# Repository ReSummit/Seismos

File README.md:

# Seismos

An evolution of the Zebra keyboard, but can be used for everyday typing. Switch between ortholinear for macro keypads and staggered for typing on the go.

Since this design utilizes daughter boards, you can even choose to move the columns around with a different rail system from the example one provided.

Allows for an interchangeable configuration between 4 and 5 row keys per column. With both halves of the keyboard, you can have a maximum of 68 keys (+2 encoder switches).

**NOTE:** If you had downloaded gerber files before December 5th, 2023, ***redownload*** the files as the RGB lights were not wired correctly. Apparently KiCAD displays the back side from the top perspective... doh! This is fixed. I also fixed the power switch so that sliding it up turns on the keyboard rather than this not being congruent on both sides.

## Pictures / Example Column Shifts:
<div style="display: flex; justify-content: center;">
    <figure>
        
    </figure>
    <figure>
        
    </figure>
    <figure>
        
    </figure>
</div>

# PCB Library Structure

NOTE: If you check the PCB for DRC errors, most of them will come from either the keyboard_reversible.pretty footprint or the switch footprints inherited from the MiRage keyboard. Since both have been used before, they can be ignored.

## Libraries
All PCBs in the `pcbs` folder refer to the footprint and symbol libraries found in `libs/Seismos-libs` as well as `libs/keyboard_reversible.pretty`.

Wait, keyboard_reversible.pretty isn't in the git clone? You need to run git submodule initialization and update with this command:
```bash
git submodule update --init --recursive
```

After this, you should not get errors on missing libraries.

## Current State of PCBs
Since release v2.0.0, there are now PCBs that incorporate the 74HC595A shift register. Thanks to drFaustroll (from QMK Discord) on an example schematic for the shift register. With this shift register, displays are now on their own I2C / SPI bus and two pins are dedicated to split communications. 2 pins are now free so I have openned up these pins at the bottom of the keyboard on the front side. These ARE NOT compatible with the I2C variants of the keyboards unless you are not using the displays and will need some modification of the firmware, so choose carefully!

***WARNING***: If you are planning to use a display on this keyboard, note that nice!view compatibility with the I2C PCBs only applies for wireless builds only! Annoyingly, the nice!view does not use an ***I2C*** interface; it uses an ***SPI*** interface to work (***whyyyyyyy***). I considered moving the CS pin to the headphone jack, but this means that one of the hardware pins for I2C is not connected so this did not happen. Normal 4 pin I2C SSD1306 displays will work for wired or wireless builds however assuming that all communications happen on I2C.

There are column and thumb cluster layouts for 4 and 5 keys (however, thumb cluster can only have 4 max). This means you can get a max total of 68 keys, plus two if you are using the rotary encoders as buttons.

For this release, there are PCBs for 4 and 5 columns. Currently, the left, right, and columns are made with a maximum size of 7x5 keys per side. Something to know is that due to routing efficiency, the column order is reversed for the right side; however, row number remains the same from top to bottom.

With release v1.1.2, the PCBs are now fully tested and ready to be used. Still, read through the notes for building this keyboard a couple sections below so you know what you're getting into.

## PCB Design Thoughts
Theoretically, since JST SH connectors are pretty small, we can possibly a maximum of 12 pins, which means that you can get at most ~7 rows per column... if the microcontroller has that many pins!

Some future design thoughts:
* A suggestion to reduce pin count is to wire the 1x4 keys as a 2x2 key setup to save pins; however, this results in a 2x2n keyboard layout, which will likely be a pain... Still interesting though to point out.
* ZMK has a pull request that introduced charlieplexing, which will reduce the pin count. If this is done per half, it may be possible to have a 70% keyboard on both sides with 10 rows per column (5 forward diodes, 5 backwards diodes). There's quite a lot of room here but currently it is still in development.

# Important notes for building keyboard

For the JST SH cables, note that the male to male connector tips should face the same side. An example one is shown below (note it is a 9 pin JST SH cale, but should be the same for 10 pin JST cables).

Example of JST SH cable with male-to-male connectors facing the same side.
<div style="display: flex; justify-content: center;">
    <figure>
        
    </figure>
</div>

Soldering the JST SH connectors is not easy! It is recommended to use the stencil design that is provided along with the stencil jig, hot plate, and solder paste. Otherwise, use a soldering iron and rely on flux!

After you are done building the core and mantle PCBs, there are example firmware files provided. Please checkout the `firmware_example` folder for more details. (Unfortunately, I haven't gotten to QMK yet, so that will have to wait for a bit)

# Required PCBs to upload

For PCBs, you will need the following:
* Minimum 2 core PCBs for left and right hands
* At least 14 mantle PCBs, 7 per core PCB
    * To save on cost, you may want to just stick with 20 of one type of mantle. 5 or 4 rows are usually enough

### **NOTE:** For the Core PCBs, you wil need to choose if you want I2C only or with a shift register starting from release v2.0.0. If you want to minimize components needed **and you are sure that you have an ATMEGA microcontroller**, you should choose I2C only. If you are not sure, you should choose I2C with shift register and just get the 74HC595A.

# BOM
## Required
* (**If using shift register version**) 2x 74HC595A SOIC-16 shift registers, though you may want extras just in case
* 28 x 10 position JST SH individual wires and connectors (preferrably 10cm long). Aliexpress has these with different colors like cable mods.
    * NOTE: For these links, they come from the same seller. Contact the seller after placing a temporary order to reduce shipping costs before paying!
    * Wires: https://www.aliexpress.us/item/3256802676433370.html (choose colors, **10 cm**, and **double head**)
        * For 5 rows, 10 cm is typically enough; you may be surprised at how far the columns can go with this. However, if you plan on changing the case design, you may need 15 cm if your columns need to go farther.
    * Connectors: https://www.aliexpress.us/item/3256802084257935.html (choose **10 pin** and **SMD Horizontal**)
* Parts that can be found from Typeractive.xyz:
    * 2 x EVQPUC02K reset button
    * 2 x SSSS811101 (alternatively on Aliexpress, MSK-12C01 or SW-12C01N-GY18)
    * 2 x 110 mAH battery (since TRRS does not have 5V, you need batteries; may change later)
* 2 x nice!nano (or Arduino Pro Micro compatible footprint)
* 56-70 x 1N4148W Diodes (variable number depending on how many keys you want)
* M3 assorted length screws (see case section for more details)
* 56-70 x MX / Choc PCB Sockets (1511 for MX or 1350 for Chocs)

## Optional
* 56-68 x SK6812MINI-E for RGB
    * 6 x per column from center of keyboard + 4 for each thumb cluster
        * Example: left and right sides require 80 total for all columns. If you only need 5 columns, then you need 68.
* 2 x nice!view (or OLED, but won't be aligned to center of microcontroller)
* 4 x 12 pin low profile socket pin headers for socketed microcontrollers (or similar)
* 2 x Rotary encoder EC11 (similar to Sofle)
* 2 x PJ320A headphone jacks 
    * **NOTE**: Due to me wanting to allow for wireless or wired setups, **the current PCB design will not charge the other keyboard side**. This is because VCC is disconnected to avoid blowing up the charging circuit of the nice!nano. If you need it, bridge the connector near one of the headphone jack pins.
* 2 x 4.7k SMD resistors for I2C. This is only needed if you plan on using I2C for split communications. There's not enough space for THT versions so uh sorry :(.

# Case
Curious to see what it looks like? Behold, OnShape link that contains questionable features that are unlabelled... This case works with the PCBs and allows for sliding rails, but won't lock the rails. A better design is in the works, but this is a good start.

Currently, a better design is in the works to place the rails underneath the PCB instead of above; this would allow the keyboard to be more low profile. For now, this works.

**This design requires the following additional parts:**
* Countersunk M3 screws:
    * 24 M3x12mm
        * Mounts down the PCB to each column plate frame into the bottom stopper
    * 3 M3x8mm
        * Holds down the rails for the keyboard
    * 14 M3x6mm
        * Corresponding nuts for the top stopper screws located near the top of each column needed
    * 2 M3x5mm
        * For the holes near the encoder and display

<p align="center">
    <p>Onshape Document (click on picture):</p>
    
</p>

# More Pictures
<div style="display: flex; justify-content: center;">
    More pictures of build:
    <figure>
        
    </figure>
    <figure>
        
    </figure>
    Development case design:
    <figure>
        
    </figure>
    <figure>
        
    </figure>
</div>

# References

Seismos uses elements found from multiple places for footprints, symbols, and even the idea.

The idea for this keyboard was inspired from the [Zebra keyboard](https://github.com/nezumee/zebra). It uses jumper cables but looks to be mainly for having a physical means to determine the layout.

For footprints, they are derived from multiple places:
* [SnapEDA](https://snapeda.com) for initial 9 position JST SH footprints and models.
* [EasyEDA](https://easyeda.com) for the power switch, reset button, and 10 position JST SH footprints as well as some models.
* [Corne](https://github.com/foostan/crkbd) repository for the SK6812MINI-E footprint.
    * Fork from [petejohanson](https://github.com/petejohanson/crkbd/tree/board/corne-ultralight) for guide on nice!view pin connections.
* [Sofle](https://github.com/josefadamcik/SofleKeyboard) keyboard for rotary encoder and headphone jack footprints.
    * [Hayden Hu's PJ320A model](https://grabcad.com/library/pj320a-pj320d-3-5mm-jack-10) was used to show the headphone jack on the 3D viewer.
    * [Dmitry Levin's EC11 encoder models](https://grabcad.com/library/11mm-metal-shaft-rotary-encoders-tht-vertical-w-push-on-switch-1) was used to show the encoder on the 3D viewer.
* [keyboard_reversible.pretty](https://github.com/50an6xy06r6n/keyboard_reversible.pretty) for easy reverse footprints made for the Pro Micro.
* [Zack Freedman's MiRage Keyboard](https://github.com/ZackFreedman/MiRage) for Choc / MX footprints with modifications to include SK6812MINI-E within the footprint.
    * [Dennis Lee's Kailh 1350 socket model](https://grabcad.com/library/kailh-1350-socket-20) was used to show the switch socket on the 3D viewer.

In the libs folder, there may be other files regarding other footprints such as the EVQPUC02K. This was found on EasyEDA on early attempts to extract the footprints.
There is also the MSK-12C02 switch. This was found from [mzst's blog](https://mzstblog.blogspot.com/2016/01/msk-12c02-smd-slider-switch-spdt-eagle.html) website, which was a good reference for the switch, but I ended up using the symbol and combined with the other footprint found from EasyEDA. Archived here as well bvecause it is nice to have a backup of it.

For firmware, there are QMK, ZMK, and KMK. Only QMK has support for shift registers at the moment but I will get to the other firmwares at some point. QMK's firmware is somewhat based from the Sofle code already on the qmk_firmware, especially the oled implementation, which is untested. Also, the LICENSE may need to be updated; will check this later.

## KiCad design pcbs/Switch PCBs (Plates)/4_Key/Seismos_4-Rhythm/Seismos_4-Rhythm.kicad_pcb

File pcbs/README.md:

# Required PCBs to upload

Thank you for downloading the PCB files! For PCBs, you will need the following:
* Minimum 2 core PCBs for left and right hands
* At least 14 mantle PCBs, 7 per core PCB
    * For cost, you may want to just stick with 20 of one type of mantle. 5 or 4 rows are usually enough

### **NOTE:** For the Core PCBs, you wil need to choose if you want I2C only or with a shift register. If you want to minimize components needed **and you are sure that you have an ATMEGA microcontroller**, you should choose I2C only. If you are not sure, you should choose I2C with shift register and just get the 74HC595A.

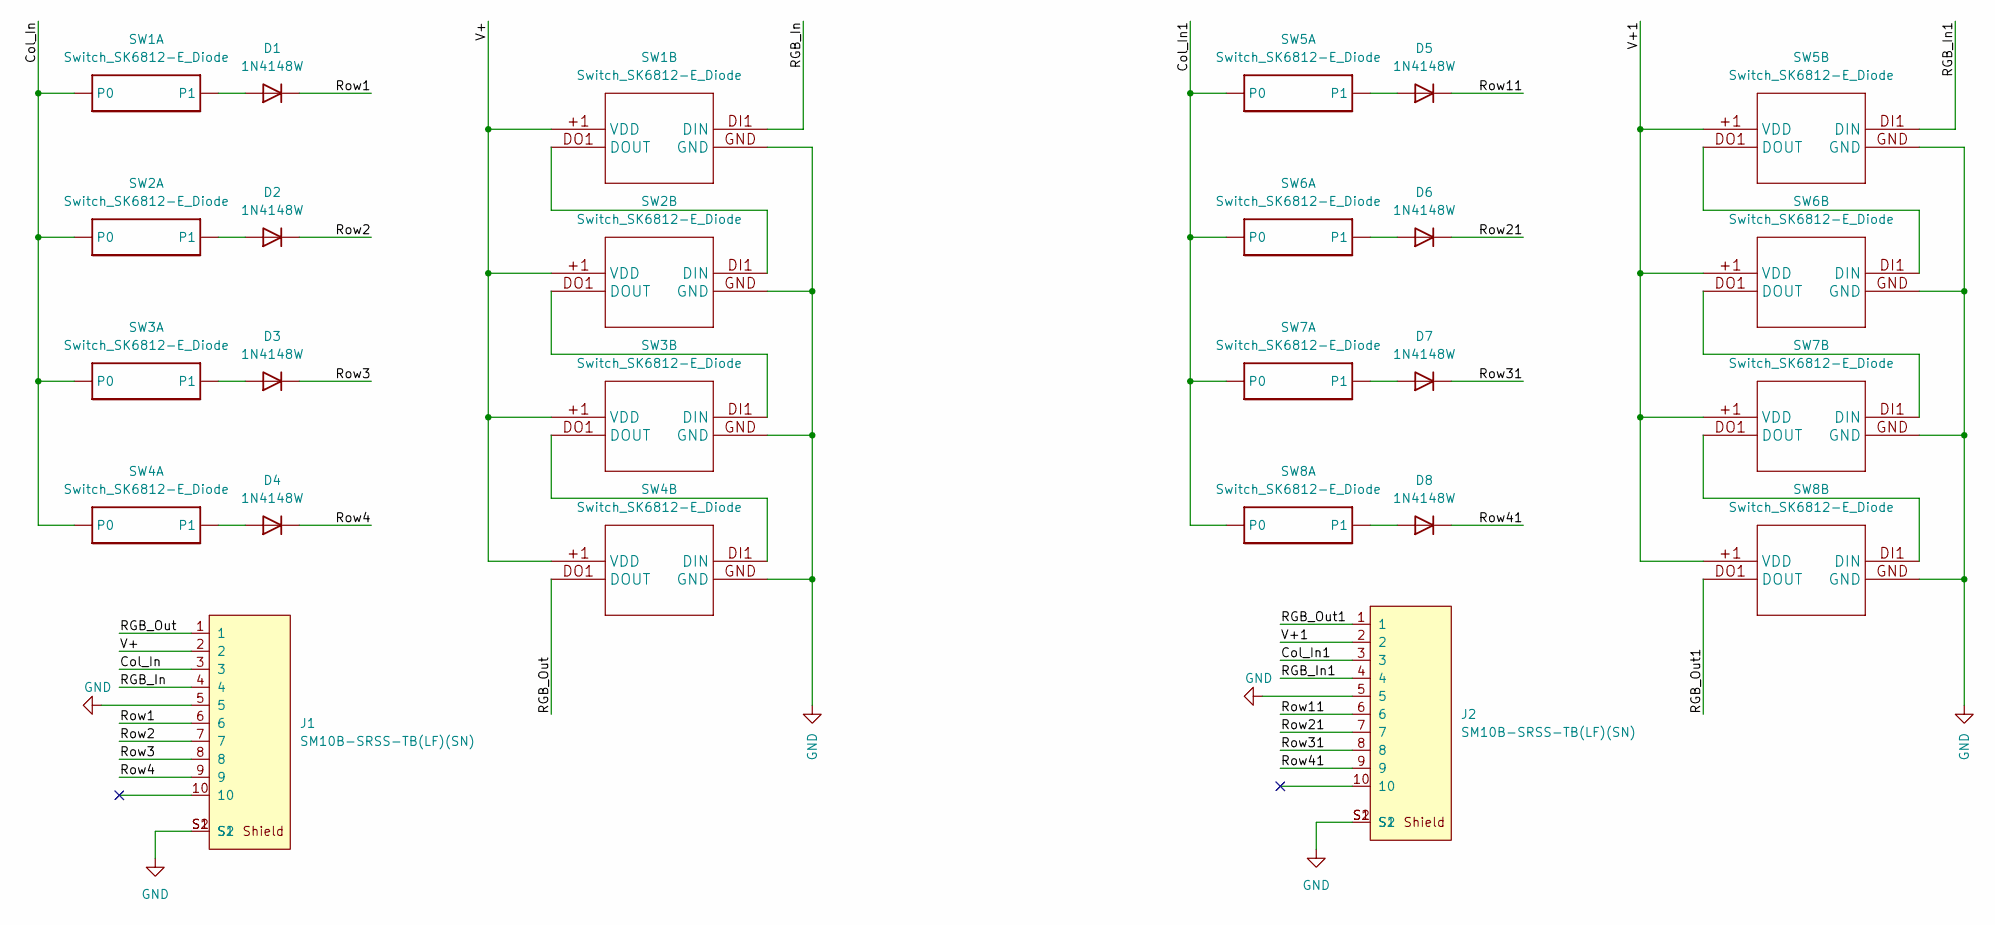
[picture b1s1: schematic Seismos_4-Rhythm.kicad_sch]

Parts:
D1, D2, D3, D4, D5, D6, D7, D8: 1N4148W; D_SOD-123
J1, J2: SM10B-SRSS-TB(LF)(SN); CONN-SMD_10P-P1.00_SM10B-SRSS-TB-LF-SN; PARTREV 1.0
SW1, SW2, SW3, SW4, SW5, SW6, SW7, SW8: Switch_SK6812-E_Diode

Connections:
/Col_In: J1.3, SW1.CHOC2 (P0), SW1.MX2 (P0), SW2.CHOC2 (P0), SW2.MX2 (P0), SW3.CHOC2 (P0), SW3.MX2 (P0), SW4.CHOC2 (P0), SW4.MX2 (P0)
/Col_In1: J2.3, SW5.CHOC2 (P0), SW5.MX2 (P0), SW6.CHOC2 (P0), SW6.MX2 (P0), SW7.CHOC2 (P0), SW7.MX2 (P0), SW8.CHOC2 (P0), SW8.MX2 (P0)
/RGB_In: J1.4, SW1.DI1 (DIN)
/RGB_In1: J2.4, SW5.DI1 (DIN)
/RGB_Out: J1.1, SW4.DO1 (DOUT)
/RGB_Out1: J2.1, SW8.DO1 (DOUT)
/Row1: D1.1 (K), J1.6
/Row2: D2.1 (K), J1.7
/Row3: D3.1 (K), J1.8
/Row4: D4.1 (K), J1.9
/Row11: D5.1 (K), J2.6
/Row21: D6.1 (K), J2.7
/Row31: D7.1 (K), J2.8
/Row41: D8.1 (K), J2.9
/V+: J1.2, SW1.+1 (VDD), SW2.+1 (VDD), SW3.+1 (VDD), SW4.+1 (VDD)
/V+1: J2.2, SW5.+1 (VDD), SW6.+1 (VDD), SW7.+1 (VDD), SW8.+1 (VDD)
GND: J1.5, J1.S1, J1.S2, J2.5, J2.S1, J2.S2, SW1.GND, SW2.GND, SW3.GND, SW4.GND, SW5.GND, SW6.GND, SW7.GND, SW8.GND
unnamed: D1.2 (A), SW1.CHOC1 (P1), SW1.MX1 (P1)
unnamed: D2.2 (A), SW2.CHOC1 (P1), SW2.MX1 (P1)
unnamed: D3.2 (A), SW3.CHOC1 (P1), SW3.MX1 (P1)
unnamed: D4.2 (A), SW4.CHOC1 (P1), SW4.MX1 (P1)
unnamed: D5.2 (A), SW5.CHOC1 (P1), SW5.MX1 (P1)
unnamed: D6.2 (A), SW6.CHOC1 (P1), SW6.MX1 (P1)
unnamed: D7.2 (A), SW7.CHOC1 (P1), SW7.MX1 (P1)
unnamed: D8.2 (A), SW8.CHOC1 (P1), SW8.MX1 (P1)
unnamed: SW1.DO1 (DOUT), SW2.DI1 (DIN)
unnamed: SW2.DO1 (DOUT), SW3.DI1 (DIN)
unnamed: SW3.DO1 (DOUT), SW4.DI1 (DIN)
unnamed: SW5.DO1 (DOUT), SW6.DI1 (DIN)
unnamed: SW6.DO1 (DOUT), SW7.DI1 (DIN)
unnamed: SW7.DO1 (DOUT), SW8.DI1 (DIN)

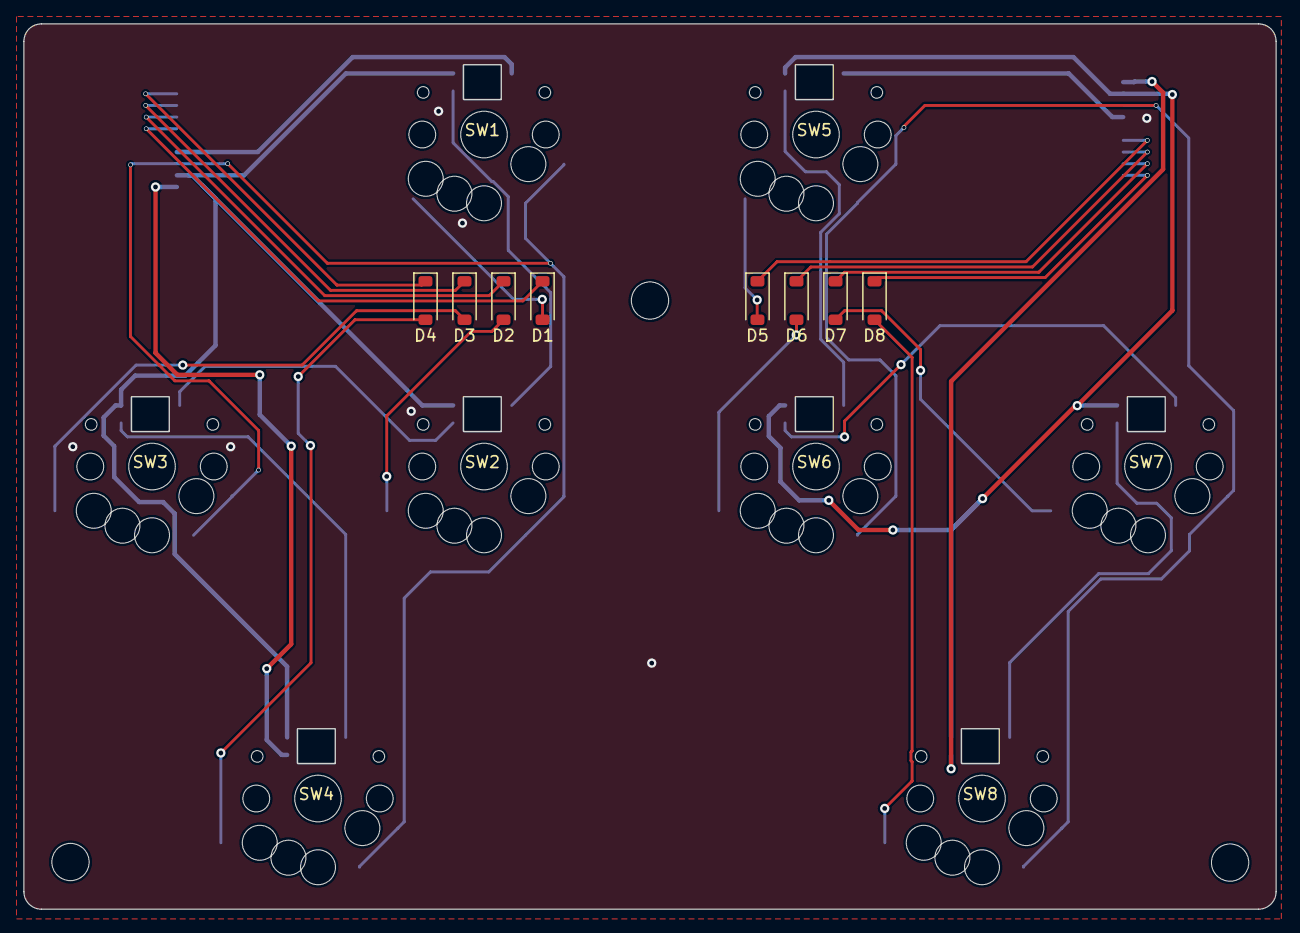
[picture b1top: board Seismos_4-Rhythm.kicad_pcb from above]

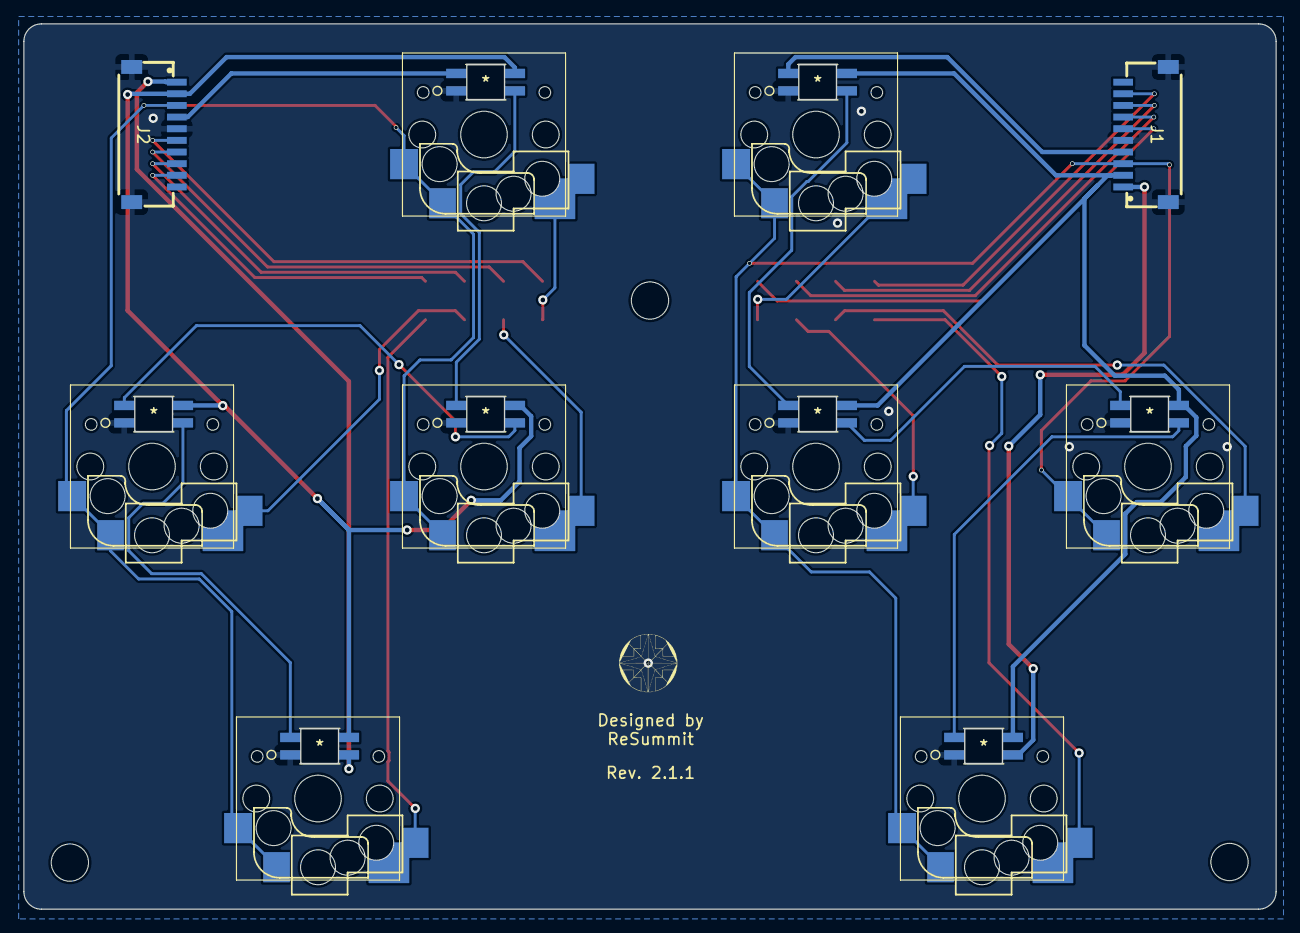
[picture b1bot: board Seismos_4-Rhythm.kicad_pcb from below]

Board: 2 copper layers, 107.5 x 76.0 mm, 18 parts (10 on the bottom side), 31 nets.

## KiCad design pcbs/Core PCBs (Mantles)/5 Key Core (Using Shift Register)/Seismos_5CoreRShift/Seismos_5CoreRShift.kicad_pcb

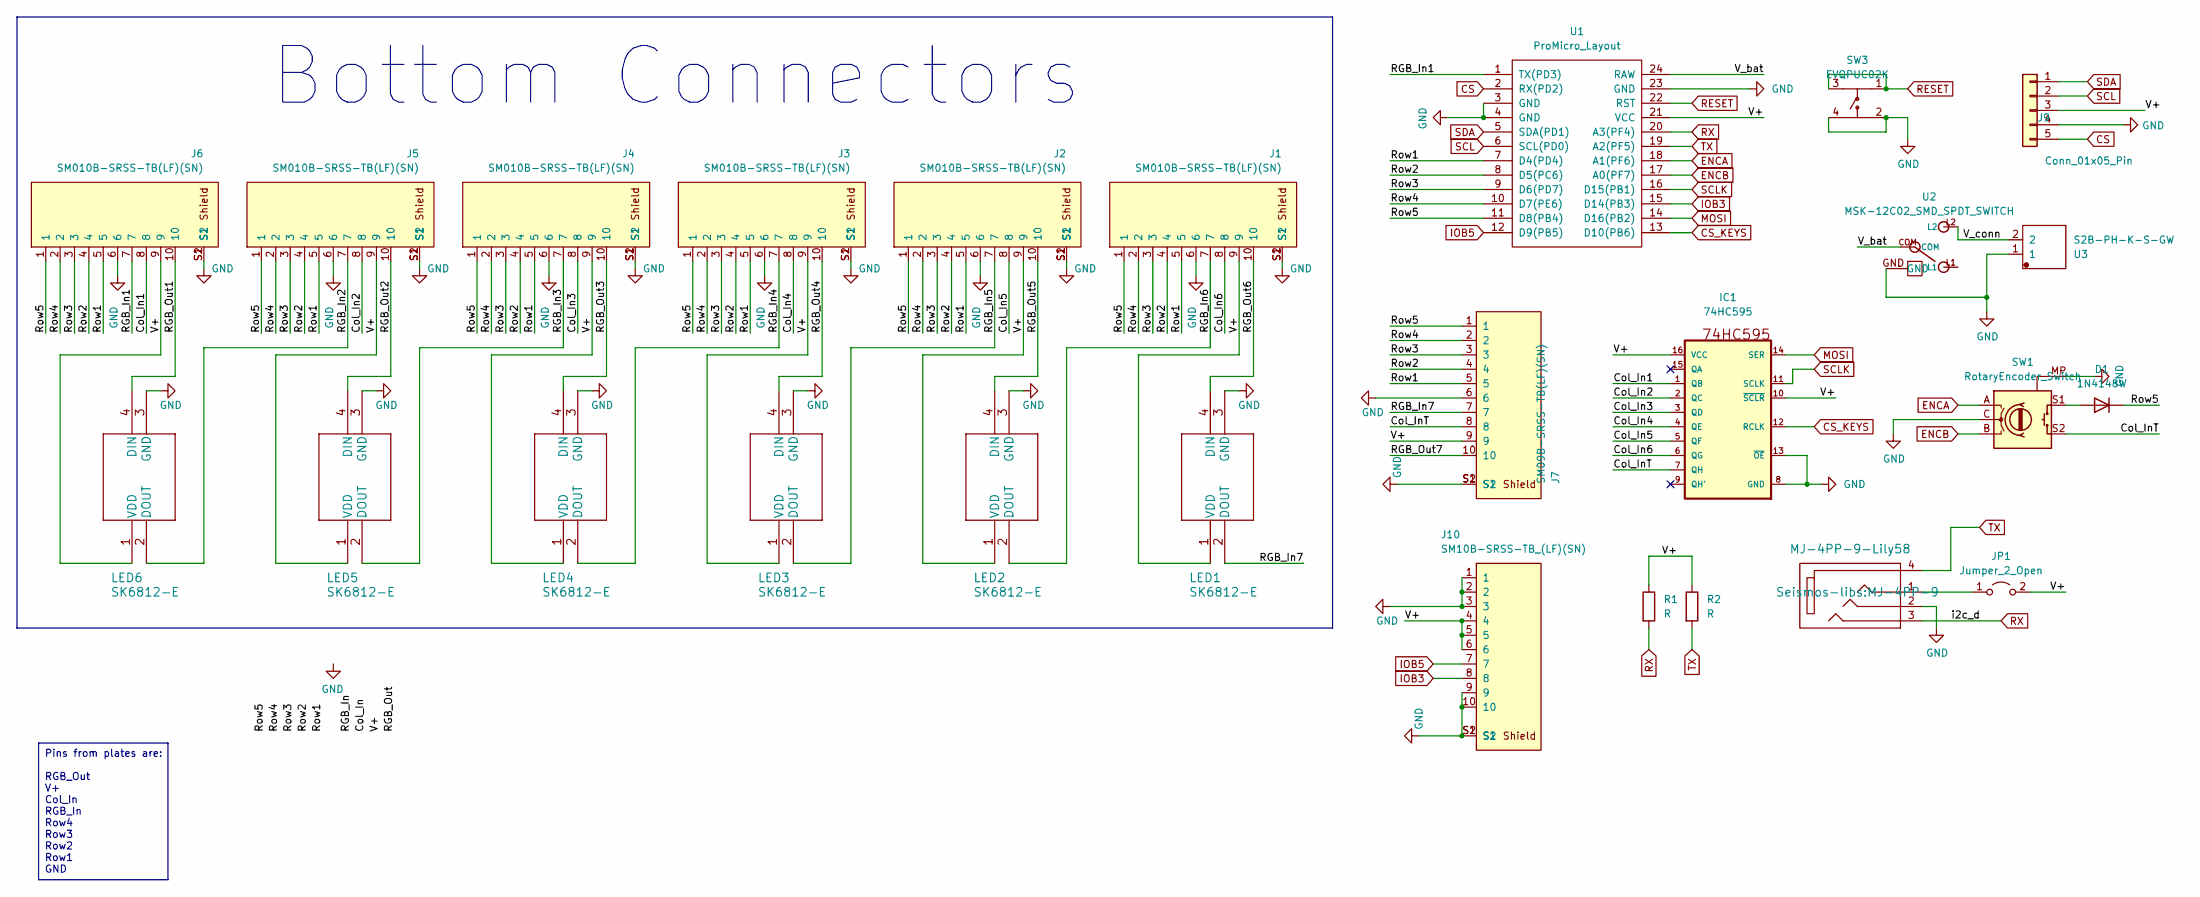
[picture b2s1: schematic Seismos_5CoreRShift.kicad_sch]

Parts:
D1: 1N4148W; D_SOD-123
IC1: 74HC595; SO16
J1, J2, J3, J4, J5, J6: SM010B-SRSS-TB(LF)(SN); CONN-SMD_10P-P1.00_SM10B-SRSS-TB-LF-SN; PARTREV 1.0
J7: SM09B-SRSS-TB(LF)(SN); CONN-SMD_10P-P1.00_SM10B-SRSS-TB-LF-SN; PARTREV 1.0
J8: MJ-4PP-9-Lily58; MJ-4PP-9
J9: Conn_01x05_Pin; PinHeader_1x05_P2.54mm_Vertical
J10: SM10B-SRSS-TB_(LF)(SN); CONN-SMD_10P-P1.00_SM10B-SRSS-TB-LF-SN; PARTREV 1.0
JP1: Jumper_2_Open; SolderJumper-2_P1.3mm_Open_TrianglePad1.0x1.5mm
LED1, LED2, LED3, LED4, LED5, LED6: SK6812-E
R1, R2: R; R_0603_1608Metric_Pad0.98x0.95mm_HandSolder
SW1: RotaryEncoder_Switch; RotaryEncoder_Alps_EC11E-Switch_Vertical_H20mm-keebio_modif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
SW3: EVQPUC02K; SW-SMD_EVQPUD02K
U1: ProMicro_Layout; keebRev-onesided_ProMicro
U2: MSK-12C02_SMD_SPDT_SWITCH; SW_PCM12SMTR
U3: S2B-PH-K-S-GW; CONN-TH_S2B-PH-K-S-GW

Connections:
/Col_In1: IC1.1 (QB), J6.8
/Col_In2: IC1.2 (QC), J5.8
/Col_In3: IC1.3 (QD), J4.8
/Col_In4: IC1.4 (QE), J3.8
/Col_In5: IC1.5 (QF), J2.8
/Col_In6: IC1.6 (QG), J1.8
/Col_InT: IC1.7 (QH), J7.8, SW1.S2
/RGB_In1: J6.7, U1.1 (TX(PD3))
/RGB_In2: J5.7, LED6.2 (DOUT)
/RGB_In3: J4.7, LED5.2 (DOUT)
/RGB_In4: J3.7, LED4.2 (DOUT)
/RGB_In5: J2.7, LED3.2 (DOUT)
/RGB_In6: J1.7, LED2.2 (DOUT)
/RGB_In7: J7.7, LED1.2 (DOUT)
/RGB_Out1: J6.10, LED6.4 (DIN)
/RGB_Out2: J5.10, LED5.4 (DIN)
/RGB_Out3: J4.10, LED4.4 (DIN)
/RGB_Out4: J3.10, LED3.4 (DIN)
/RGB_Out5: J2.10, LED2.4 (DIN)
/RGB_Out6: J1.10, LED1.4 (DIN)
/RGB_Out7: J7.10
/Row1: J1.5, J2.5, J3.5, J4.5, J5.5, J6.5, J7.5, U1.7 (D4(PD4))
/Row2: J1.4, J2.4, J3.4, J4.4, J5.4, J6.4, J7.4, U1.8 (D5(PC6))
/Row3: J1.3, J2.3, J3.3, J4.3, J5.3, J6.3, J7.3, U1.9 (D6(PD7))
/Row4: J1.2, J2.2, J3.2, J4.2, J5.2, J6.2, J7.2, U1.10 (D7(PE6))
/Row5: D1.1 (K), J1.1, J2.1, J3.1, J4.1, J5.1, J6.1, J7.1, U1.11 (D8(PB4))
/V+: IC1.10 (~SCLR), IC1.16 (VCC), J1.9, J2.9, J3.9, J4.9, J5.9, J6.9, J7.9, J9.3, J10.4, J10.5, J10.6, JP1.2 (B), LED1.1 (VDD), LED2.1 (VDD), LED3.1 (VDD), LED4.1 (VDD), LED5.1 (VDD), LED6.1 (VDD), R1.1, R2.1, U1.21 (VCC)
/V_bat: U1.24 (RAW), U2.COM
/V_conn: U2.L2, U3.2
CS: J9.5, U1.2 (RX(PD2))
CS_KEYS: IC1.12 (RCLK), U1.13 (D10(PB6))
ENCA: SW1.A, U1.18 (A1(PF6))
ENCB: SW1.B, U1.17 (A0(PF7))
GND: IC1.8 (GND), IC1.13 (~OE), J1.6, J1.S1, J1.S2, J2.6, J2.S1, J2.S2, J3.6, J3.S1, J3.S2, J4.6, J4.S1, J4.S2, J5.6, J5.S1, J5.S2, J6.6, J6.S1, J6.S2, J7.6, J7.S1, J7.S2, J8.2, J9.4, J10.1, J10.2, J10.3, J10.9, J10.10, J10.S1, J10.S2, LED1.3 (GND), LED2.3 (GND), LED3.3 (GND), LED4.3 (GND), LED5.3 (GND), LED6.3 (GND), SW1.C, SW1.MP, SW3.2, SW3.4, U1.3 (GND), U1.4 (GND), U1.23 (GND), U2.GND, U3.1
IOB3: J10.8, U1.15 (D14(PB3))
IOB5: J10.7, U1.12 (D9(PB5))
MOSI: IC1.14 (SER), U1.14 (D16(PB2))
unnamed: D1.2 (A), SW1.S1
unnamed: J8.1, JP1.1 (A)
RESET: SW3.1, SW3.3, U1.22 (RST)
RX: J8.3, R1.2, U1.20 (A3(PF4))
SCL: J9.2, U1.6 (SCL(PD0))
SCLK: IC1.11 (SCLK), U1.16 (D15(PB1))
SDA: J9.1, U1.5 (SDA(PD1))
TX: J8.4, R2.2, U1.19 (A2(PF5))

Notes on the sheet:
Pins from plates are: RGB_Out V+ Col_In RGB_In Row4 Row3 Row2 Row1 GND
Bottom Connectors

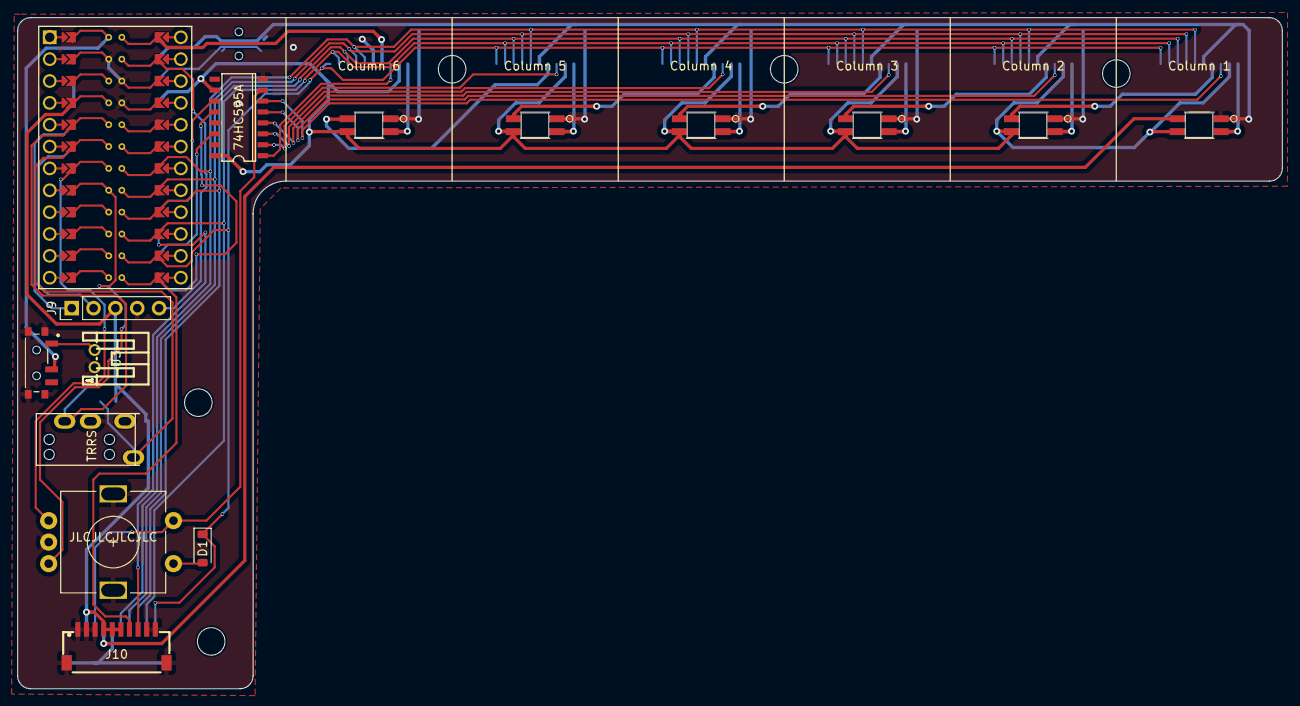
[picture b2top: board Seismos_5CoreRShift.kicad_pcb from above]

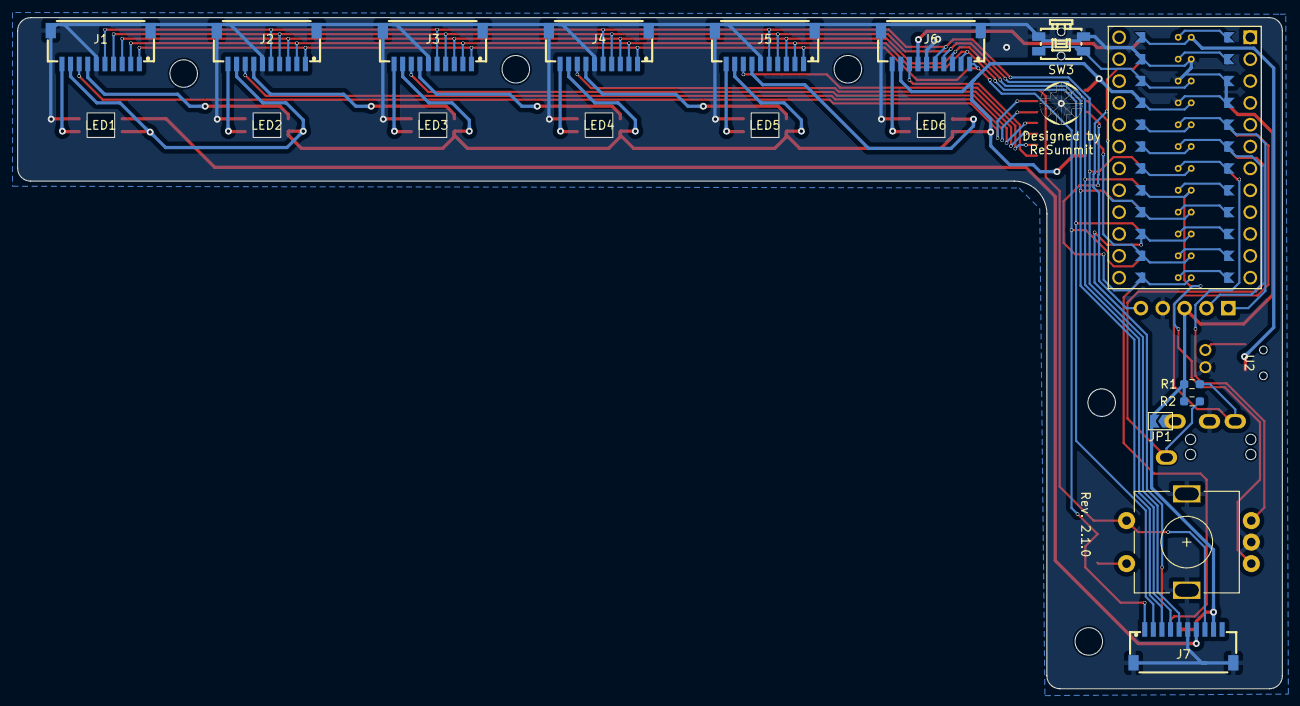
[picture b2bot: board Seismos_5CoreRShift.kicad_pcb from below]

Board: 2 copper layers, 147.0 x 78.0 mm, 26 parts (11 on the bottom side), 44 nets.

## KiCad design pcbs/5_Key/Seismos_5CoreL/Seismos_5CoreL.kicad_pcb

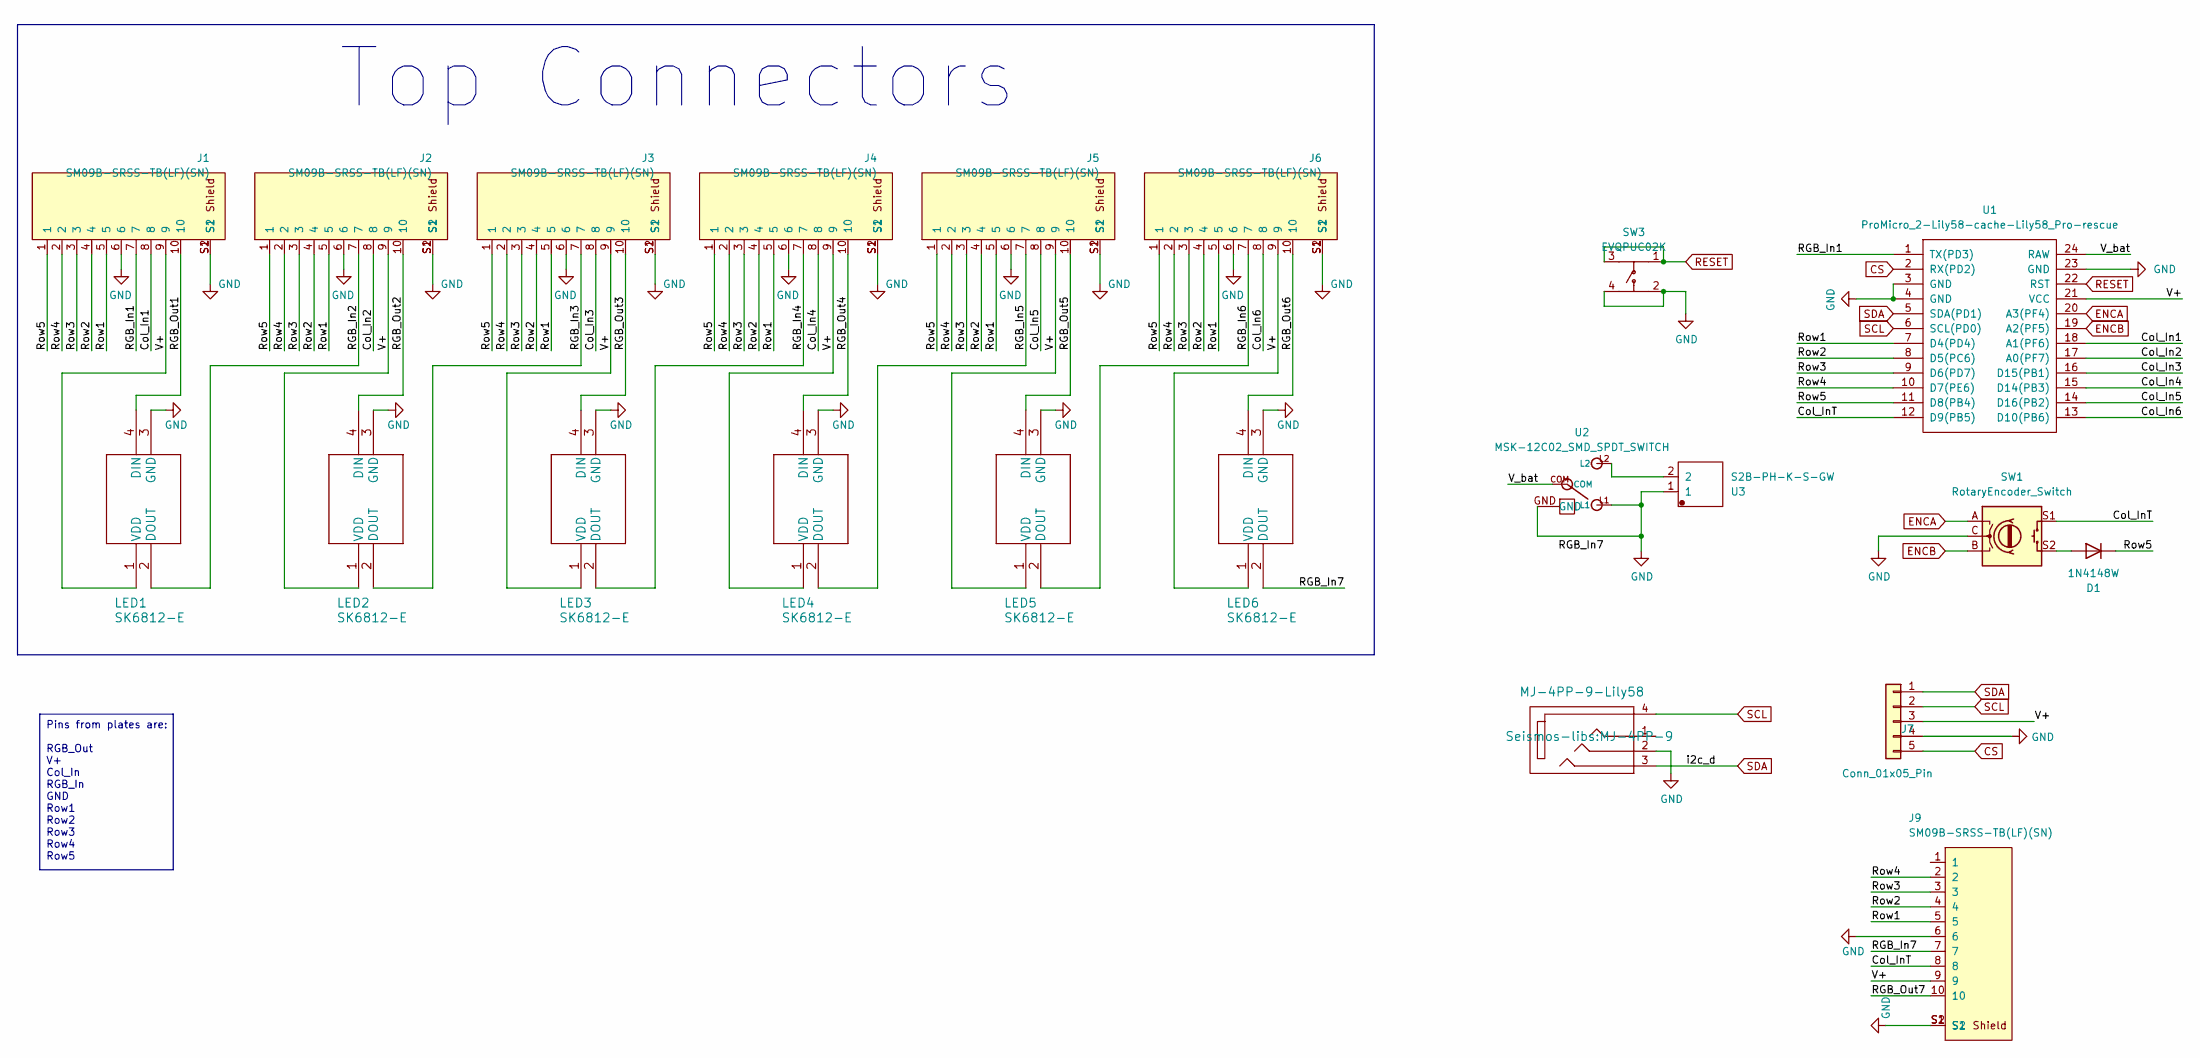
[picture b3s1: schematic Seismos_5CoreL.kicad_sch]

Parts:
D1: 1N4148W; D_SOD-123
J1, J2, J3, J4, J5, J6, J9: SM09B-SRSS-TB(LF)(SN); CONN-SMD_10P-P1.00_SM10B-SRSS-TB-LF-SN; PARTREV 1.0
J7: Conn_01x05_Pin; PinHeader_1x05_P2.54mm_Vertical
J8: MJ-4PP-9-Lily58; MJ-4PP-9
LED1, LED2, LED3, LED4, LED5, LED6: SK6812-E
SW1: RotaryEncoder_Switch; RotaryEncoder_Alps_EC11E-Switch_Vertical_H20mm-keebio_modif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
SW3: EVQPUC02K; SW-SMD_EVQPUD02K
U1: ProMicro_2-Lily58-cache-Lily58_Pro-rescue; ProMicro
U2: MSK-12C02_SMD_SPDT_SWITCH; SW_PCM12SMTR
U3: S2B-PH-K-S-GW; CONN-TH_S2B-PH-K-S-GW

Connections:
/Col_In1: J1.8, U1.18 (A1(PF6))
/Col_In2: J2.8, U1.17 (A0(PF7))
/Col_In3: J3.8, U1.16 (D15(PB1))
/Col_In4: J4.8, U1.15 (D14(PB3))
/Col_In5: J5.8, U1.14 (D16(PB2))
/Col_In6: J6.8, U1.13 (D10(PB6))
/Col_InT: J9.8, SW1.S1, U1.12 (D9(PB5))
/RGB_In1: J1.7, U1.1 (TX(PD3))
/RGB_In2: J2.7, LED1.2 (DOUT)
/RGB_In3: J3.7, LED2.2 (DOUT)
/RGB_In4: J4.7, LED3.2 (DOUT)
/RGB_In5: J5.7, LED4.2 (DOUT)
/RGB_In6: J6.7, LED5.2 (DOUT)
/RGB_In7: J9.7, LED6.2 (DOUT)
/RGB_Out1: J1.10, LED1.4 (DIN)
/RGB_Out2: J2.10, LED2.4 (DIN)
/RGB_Out3: J3.10, LED3.4 (DIN)
/RGB_Out4: J4.10, LED4.4 (DIN)
/RGB_Out5: J5.10, LED5.4 (DIN)
/RGB_Out6: J6.10, LED6.4 (DIN)
/RGB_Out7: J9.10
/Row1: J1.5, J2.5, J3.5, J4.5, J5.5, J6.5, J9.5, U1.7 (D4(PD4))
/Row2: J1.4, J2.4, J3.4, J4.4, J5.4, J6.4, J9.4, U1.8 (D5(PC6))
/Row3: J1.3, J2.3, J3.3, J4.3, J5.3, J6.3, J9.3, U1.9 (D6(PD7))
/Row4: J1.2, J2.2, J3.2, J4.2, J5.2, J6.2, J9.2, U1.10 (D7(PE6))
/Row5: D1.1 (K), J1.1, J2.1, J3.1, J4.1, J5.1, J6.1, U1.11 (D8(PB4))
/V+: J1.9, J2.9, J3.9, J4.9, J5.9, J6.9, J7.3, J9.9, LED1.1 (VDD), LED2.1 (VDD), LED3.1 (VDD), LED4.1 (VDD), LED5.1 (VDD), LED6.1 (VDD), U1.21 (VCC)
/V_bat: U1.24 (RAW), U2.COM
CS: J7.5, U1.2 (RX(PD2))
ENCA: SW1.A, U1.20 (A3(PF4))
ENCB: SW1.B, U1.19 (A2(PF5))
GND: J1.6, J1.S1, J1.S2, J2.6, J2.S1, J2.S2, J3.6, J3.S1, J3.S2, J4.6, J4.S1, J4.S2, J5.6, J5.S1, J5.S2, J6.6, J6.S1, J6.S2, J7.4, J8.2, J9.6, J9.S1, J9.S2, LED1.3 (GND), LED2.3 (GND), LED3.3 (GND), LED4.3 (GND), LED5.3 (GND), LED6.3 (GND), SW1.C, SW3.2, SW3.4, U1.3 (GND), U1.4 (GND), U1.23 (GND), U2.GND, U2.L1, U3.1
unnamed: D1.2 (A), SW1.S2
unnamed: U2.L2, U3.2
RESET: SW3.1, SW3.3, U1.22 (RST)
SCL: J7.2, J8.4, U1.6 (SCL(PD0))
SDA: J7.1, J8.3, U1.5 (SDA(PD1))

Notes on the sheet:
Pins from plates are: RGB_Out V+ Col_In RGB_In GND Row1 Row2 Row3 Row4 Row5
Top Connectors

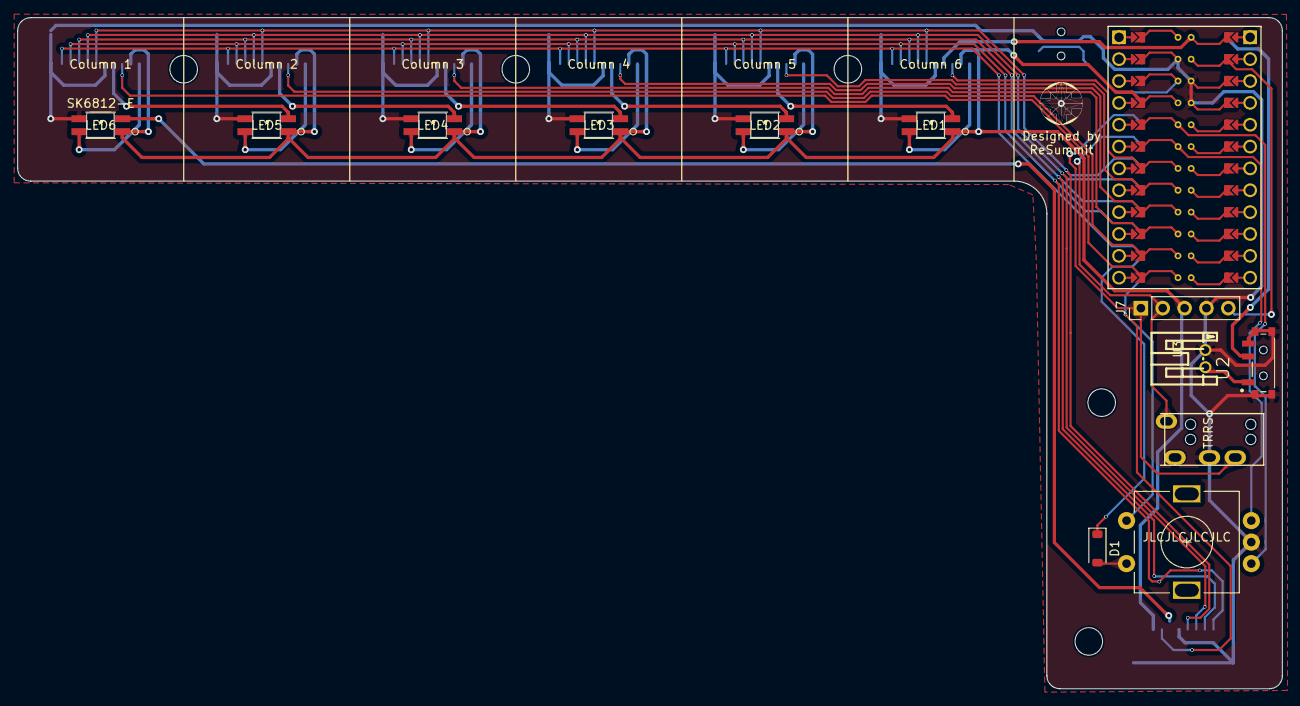
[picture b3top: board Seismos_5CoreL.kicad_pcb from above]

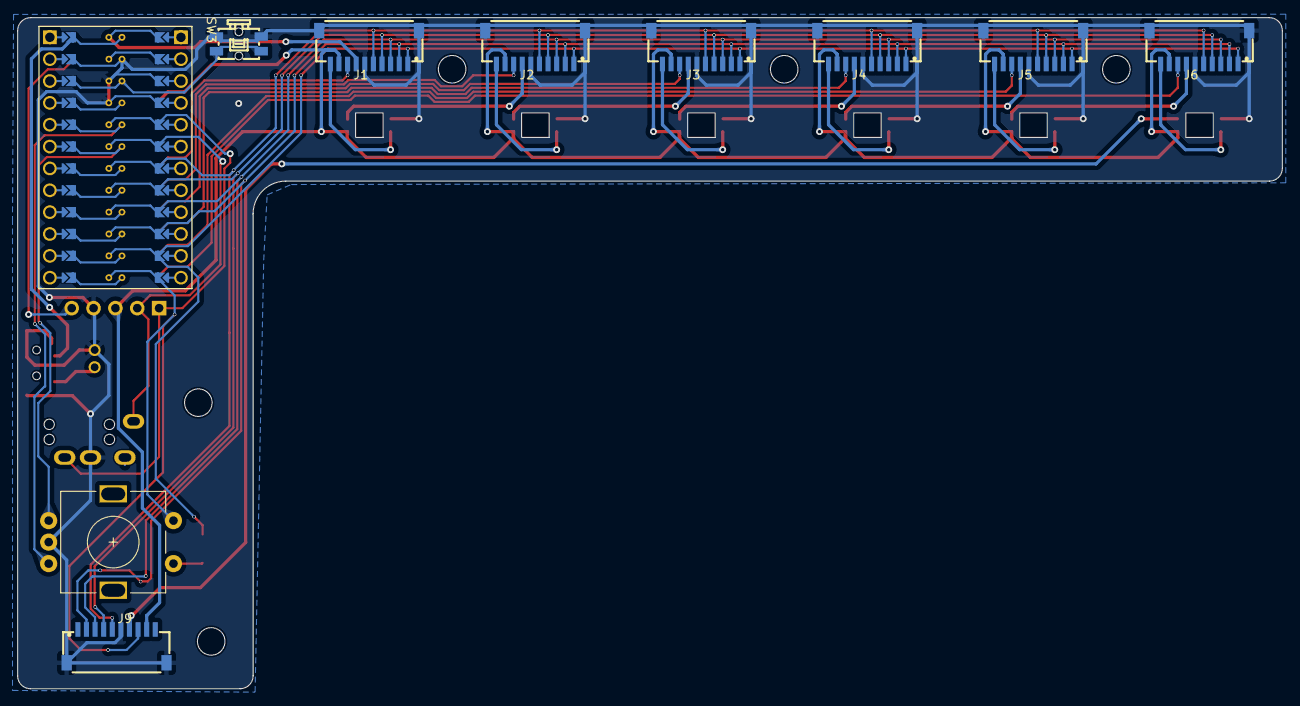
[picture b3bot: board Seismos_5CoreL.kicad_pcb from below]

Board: 2 copper layers, 147.0 x 78.0 mm, 23 parts (14 on the bottom side), 36 nets.

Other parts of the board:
2, 4: Hole_M3_3.2mm

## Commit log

2023-10-15 Initial commit, add libs
    Add PCB files and files used for footprints and symbols
    Some symbols are derived from Lily58 and Corne but will update this in
    the README later.
2023-10-15 Create PCB STEP Files
    Generated STEP files.
2023-10-15 Update 4Key Column STEP
    Wrong footprint definitions resulted in no parts shown so fixed it
2023-10-16 Add README for viewing pleasure
2023-10-16 Added README flair
2023-10-16 Forgot a colon in README
2023-10-16 Specificity error
2023-10-16 Forgot to add link to Zebra keyboard
2023-10-17 Fix footprint errors and new 2x2 PCB
    Fixed keyboard_reversible.pretty not being included.
    Added a 2x2 PCB for the thumb.
    Added a note regarding DRC errors involving two specific footprints...
2023-10-17 Refresh Export of PCB
2023-10-17 Fix 4Key Column Hole Size
    Converted the M3 holes to the standard footprint instead of edge cut
    layer drawing of a circle. Also updated names of gerber output folders.
2023-10-17 Add gitignore for zip files
2023-10-17 Replaced microvias with very small vias
    Also added small JLCJLCJLCJLC text for JLCPCB.
    JLCPCB doesn't allow for blind microvias... so annoyingly I had to
    reroute the row and column wiring. Luckily the 4 key doesn't use
    microvias so that one is okay.
2023-10-17 Replaced microvias in CoreL
    I happened to find more... in CoreL only. CoreR looks mostly fine.
2023-10-18 Last look over CoreL and removed microvias
    CoreR has been verified by JLCPCB and is good to go. I forgot to add
    teardrops to it so it is now added. CoreL on the other hand had some
    more microvias near the JST SH conectors and under the rotary
    encoder. These have been removed.
    NOTE: Due to the microvia conversion, the previous commit was when the
    NTPH holes near the columns have been shifted down by 0.5 mm. This will
2023-10-19 Add another layout example for pics
2023-10-19 Weird README layout fix attempt
2023-10-19 README format attempt 2
2023-10-19 Pictures change to markdown format
2023-10-19 Maybe this time...?
2023-10-19 Resize pics
2023-10-19 HTML picture markdown is weird
2023-10-19 Changed ref label for logo to comment
2023-10-19 Update 3D PCB STEP models
2023-10-20 Completed Thumb 2x2 module
2023-10-22 5 key variant release!
    Well... thought 5 key variant would be a lot of work but it turns out
    that it isn't too much. This uses up ALL the pins on the arduino micro
    however and unfortunately, a 5 key version for the thumb isn't possible
    because one of the keys is used by the encoder.
    WARNING: This is NOT compatible with the 4 key version yet. This is
    specific to the column PCBs (4-Key and 4Thumb). In the next commit, I
2023-10-22 Seismos PCB v1.0rc
    First preliminary release of PCB with support for 7 columns and 5 rows.
    Folders have now been restructured to organize between cores and mantles.
    Cores are the baseboard/motherboard of the keyboard.
    Mantles are the connections between the switches and the core.
    Of course, additional modules can be made for both cores and mantles.
    If you have more pins, larger modules are possible!
2023-10-22 Update 3D models and upload gerbers
2023-10-22 JST SH cable text rearranged
2023-10-22 Make cable image bigger
2023-10-28 Update STEP files
2023-11-11 Added stencils for new and old PCBs
    Created stencils for solder pasting PCBs with the core and plates.
    I ordered both new and old versions so two stencils were made; however,
    the holes for the old variant are misaligned. For this, use the other
    aligning holes.
    In addition, repaired footprints for switches where the switch footprint
    was appearing on the reverse side. This is now fixed.
2023-12-05 Modify case files and stencil, as well as fix thumb cluster
2023-12-05 Release v1.1
    ***NOTE***: If you have a previous commit, please update your files.
    This commit fixes the incorrect RGB pinout and power switch as the
    RGB footprint was incorrect.
    The power switch behaviour is also fixed in this commit so the position
    matches on both sides.
2023-12-08 Update README
    Add specific BOM numbers that are needed for keyboard,
    plus suggestion for charlieplex columns and development pictures
2023-12-08 Fix schematic reference errors for thumb
    Errors appeared when applying thumb schematic to PCB.
    This doesn't change the PCB footprints though, so no re-release
2023-12-09 Release v1.1.1
    Added I2C pull up resistors and bridge contacts on the backif 5V power
    is desired. If you have v1.1, V+ is actually close to the headphone
    jack, so you can scratch off the trace and bridge there.
2023-12-09 Forgot to save, also update gerbers
2023-12-27 Fix right encoder button, fix connector refs
    Right side encoder was still connected to the 6th column for some
    reason... Figures when you copy paste the same board design into a
    different project.
    Also fixed references for the SH connectors, so it doesn't look weird
2023-12-27 Force upload updated gerbers
2023-12-27 Update readme and include firmware files
2023-12-27 Fix right side encoder mount to ground
2023-12-28 Update example firmware files for KMK
2024-01-06 Update README.md
    Nice!view displays are not nice at all (uses SPI instead of I2C)
2024-01-21 Added 74HC595A support, new release
    New PCB versions supporting shift register.
    Another JST SH connector is added to expose 2 spare pins.
    Footprints for microcontroller were updated using modified footprint from library.
    Original variants updated to these new footprints with some fixes as well.
2024-01-21 Upload updated gerbers
2024-01-21 Specify SOIC-16 needed
2024-02-11 Add QMK firmware, fix extra IC ref on right
2024-02-11 Update rules.mk for rp2040 conversion, also readme
2024-05-02 HOTFIX, power switch bridges to ground
2024-05-03 Update PCB version and gerbers for HOTFIX
2024-05-11 Add rhythm game module

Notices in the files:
parts and their libraries:
Copyright 2021 Accelerated Designs. All rights reserved.
